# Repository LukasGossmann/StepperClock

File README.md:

# The clockwork
The clock hands are moved by 2 Nema8 double shaft stepper motors (one hollow shaft and one normal one).  
To allow the clock to move its hands smoothly and nearly completely silently the stepper motors are driven using 2 Trinamic TMC2209 SilentStepStick modules configured for 256x microstepping. `200 full steps * 256 micro steps = 51200 steps per rev`  
The structural parts of the clockwork are CNC cut from 3mm Resopal and slotted together.  
Unfortunately i mostly forgot to take pictures of the build process and the finished clockwork before installing it so only the CAD drawings show how everything fits together.

# The pendulum

Its driven by a small electromagnet at the frequency that the pendulum would naturally swing at.  
`Pendulum length = 350mm, Frequency = 0.8425Hz`  
The brass ring was made using a small ring rolling / metal bending machine and soldered together at the seam.  
For additional rigidity the pendulum shaft goes through the ring and is soldered to it at both the top and bottom.  
Inside of the ring are 2 circular slices of purple heart wood with slots for the shaft to pass through.  
They are just press fit in place and can be removed with a suction cup in case the brass needs to be re-polished.  

# The bell mechanism
Originally the design of the clock included a 5 tone bell mechanism that used solenoids which hit against brass rods.  
This part of the design was later abandoned due to the bells not sounding that good.  
The new design of the clockwork no longer includes the bells.  
There is a few pictures of the old assembly in the pictures folder.

<br clear="right"/>

# The dial plate

Its made from Corian that has been engraved with a 1mm carbide endmill.  
The engraving was then filled with black epoxy and a brass ring.  
After that everything was sanded flush and polished.  

<br clear="left"/>

# The electronics
The brain of this clock is a Raspberry Pi Pico. In total 4 PWM units are used to control the clock. 2 PWM units are used to drive the hands.  
The first PWM unit drives the minute hand at `(200 full steps * 256 microstepping)/(60 seconds * 60 minutes) = 14.22222222222222222Hz` which is still within reach of the PWM unit at normal system clock speeds.  
However the hour hand needs a step pulse at just 1/12th of this frequency `1.18518518519Hz` which is way too low for the PWM units to reach.  
So instead of generating the hour pulse directly, the second PWM unit is configured to be driven by the output of first pwn unit (using an external jumper) and just divides the frequency by 12.  
  
The same idea is also used to drive the very low frequency PWM output for the pendulum.  
In that case a 10khz clock is divided down to the desired frequency and the pulse width is adjustable as well for different power supply voltages.  

The time can be set through a text prompt via a USB serial terminal.  
When the time is set the clock hands automatically home, using 2 optical limit switches, and after that drive to the set time.  
At night the clock also goes into a power saving mode where the clock hands and the pendulum stop moving.  
When powering back up the clock hands home again and drive to the current time.  

There is unfortunately not very many pictures of the PCB itself because i again forgot to take pictures.  
I managed to find it in the background of some pictures of other projects though so i cropped out the unimportant bits (which is also why the quality of those pictures isn't great...)

<br clear="left"/>

# The lock

The lock is custom designed for this clock. It can be used for all types of full overlay doors when the door is at least 12mm or so thick (the lock is just 9mm thick).  
Once installed the lock and latch plate don't take up any space inside whatever enclosure they are used in.  
The latch of the lock is moved using an eccentric cam whose center of rotation is the key shaft.  
A small plastic spring is used to give some audible and haptic feedback on when the key has been rotated far enough.  

<br clear="right"/>

# The case
It was actually build as my journeyman's piece for the apprenticeship as a carpenter I completed in August of 2023.  
The case consists of 2 big half circles that were made by gluing ten 2mm pieces of veneer together while clamped to a mold.  
After the glue dries the pieces keep the shape and are actually surprisingly stiff.  
All the relevant documents that have to be submitted (Drawings, Concept, etc.) to get the project approved are also available in this repository for anyone interested.  
That is also why the repository contains a mix of German and English.  
To document the build process and show how certain things were made (in case anyone wants to replicate the project) I took a lot of pictures while building it.  
The clock was on display at the Forum Alstertal in Hamburg, Germany at the yearly exhibition of carpentry journeyman's pieces:  
`30th of June to the 05th July 2023`  
[Link to the event](https://www.forum-alstertal.de/news_veranstaltungen_detail_394.html)

# Awards

During the exhibition the residents living at the Forum Alstertal get the opportunity to vote on their favorite piece.
This year my clock won the audience award.

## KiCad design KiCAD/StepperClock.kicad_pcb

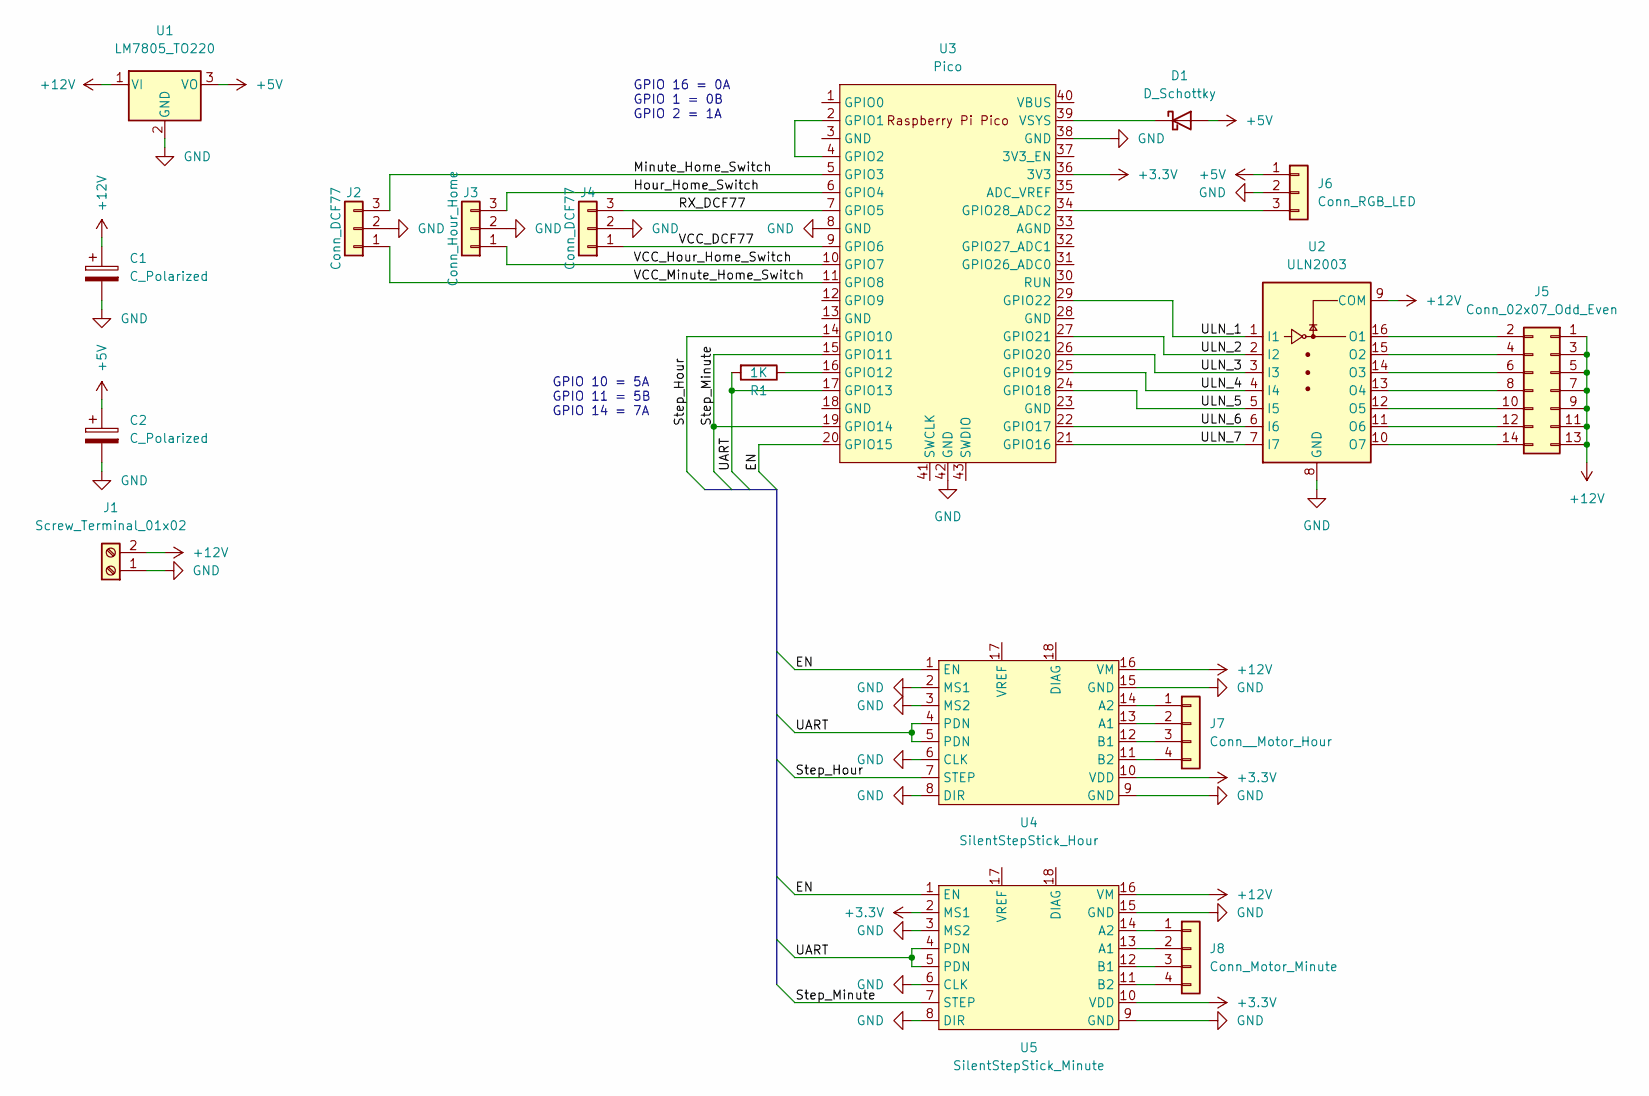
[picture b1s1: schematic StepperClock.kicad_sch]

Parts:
C1, C2: C_Polarized; CP_Radial_D10.0mm_P5.00mm_P7.50mm
D1: D_Schottky; D_DO-15_P10.16mm_Horizontal
J1: Screw_Terminal_01x02; TerminalBlock_RND_205-00232_1x02_P5.08mm_Horizontal
J2, J4: Conn_DCF77; PinHeader_1x03_P2.54mm_Vertical
J3: Conn_Hour_Home; PinHeader_1x03_P2.54mm_Vertical
J5: Conn_02x07_Odd_Even; PinHeader_2x07_P2.54mm_Vertical
J6: Conn_RGB_LED; PinHeader_1x03_P2.54mm_Vertical
J7: Conn__Motor_Hour; PinHeader_1x04_P2.54mm_Vertical
J8: Conn_Motor_Minute; PinHeader_1x04_P2.54mm_Vertical
R1: 1K; R_Axial_DIN0207_L6.3mm_D2.5mm_P10.16mm_Horizontal
U1: LM7805_TO220; TO-220-3_Vertical
U2: ULN2003; SOIC-16_3.9x9.9mm_P1.27mm
U3: Pico; RPi_Pico_SMD_TH
U4: SilentStepStick_Hour; SilentStepStick
U5: SilentStepStick_Minute; SilentStepStick

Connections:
+3.3V: U3.36 (3V3), U4.10 (VDD), U5.2 (MS1), U5.10 (VDD)
+5V: C2.1, D1.2 (A), J6.1, U1.3 (VO)
+12V: C1.1, J1.2, J5.1, J5.3, J5.5, J5.7, J5.9, J5.11, J5.13, U1.1 (VI), U2.9 (COM), U4.16 (VM), U5.16 (VM)
/EN: U3.20 (GPIO15), U4.1 (EN), U5.1 (EN)
/Hour_Home_Switch: J3.3, U3.6 (GPIO4)
/Minute_Home_Switch: J2.3, U3.5 (GPIO3)
/RX_DCF77: J4.3, U3.7 (GPIO5)
/Step_Hour: U3.14 (GPIO10), U4.7 (STEP)
/Step_Minute: U3.15 (GPIO11), U3.19 (GPIO14), U5.7 (STEP)
/UART: R1.2, U3.17 (GPIO13), U4.4 (PDN), U4.5 (PDN), U5.4 (PDN), U5.5 (PDN)
/ULN_1: U2.1 (I1), U3.29 (GPIO22)
/ULN_2: U2.2 (I2), U3.27 (GPIO21)
/ULN_3: U2.3 (I3), U3.26 (GPIO20)
/ULN_4: U2.4 (I4), U3.25 (GPIO19)
/ULN_5: U2.5 (I5), U3.24 (GPIO18)
/ULN_6: U2.6 (I6), U3.22 (GPIO17)
/ULN_7: U2.7 (I7), U3.21 (GPIO16)
/VCC_DCF77: J4.1, U3.9 (GPIO6)
/VCC_Hour_Home_Switch: J3.1, U3.10 (GPIO7)
/VCC_Minute_Home_Switch: J2.1, U3.11 (GPIO8)
GND: C1.2, C2.2, J1.1, J2.2, J3.2, J4.2, J6.2, U1.2 (GND), U2.8 (GND), U3.8 (GND), U3.38 (GND), U3.42 (GND), U4.2 (MS1), U4.3 (MS2), U4.6 (CLK), U4.8 (DIR), U4.9 (GND), U4.15 (GND), U5.3 (MS2), U5.6 (CLK), U5.8 (DIR), U5.9 (GND), U5.15 (GND)
unnamed: D1.1 (K), U3.39 (VSYS)
unnamed: J5.2, U2.16 (O1)
unnamed: J5.4, U2.15 (O2)
unnamed: J5.6, U2.14 (O3)
unnamed: J5.8, U2.13 (O4)
unnamed: J5.10, U2.12 (O5)
unnamed: J5.12, U2.11 (O6)
unnamed: J5.14, U2.10 (O7)
unnamed: J6.3, U3.34 (GPIO28_ADC2)
unnamed: J7.1, U4.14 (A2)
unnamed: J7.2, U4.13 (A1)
unnamed: J7.3, U4.12 (B1)
unnamed: J7.4, U4.11 (B2)
unnamed: J8.1, U5.14 (A2)
unnamed: J8.2, U5.13 (A1)
unnamed: J8.3, U5.12 (B1)
unnamed: J8.4, U5.11 (B2)
unnamed: U3.2 (GPIO1), U3.4 (GPIO2)
unnamed: R1.1, U3.16 (GPIO12)

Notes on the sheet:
GPIO 16 = 0A GPIO 1 = 0B GPIO 2 = 1A
GPIO 10 = 5A GPIO 11 = 5B GPIO 14 = 7A

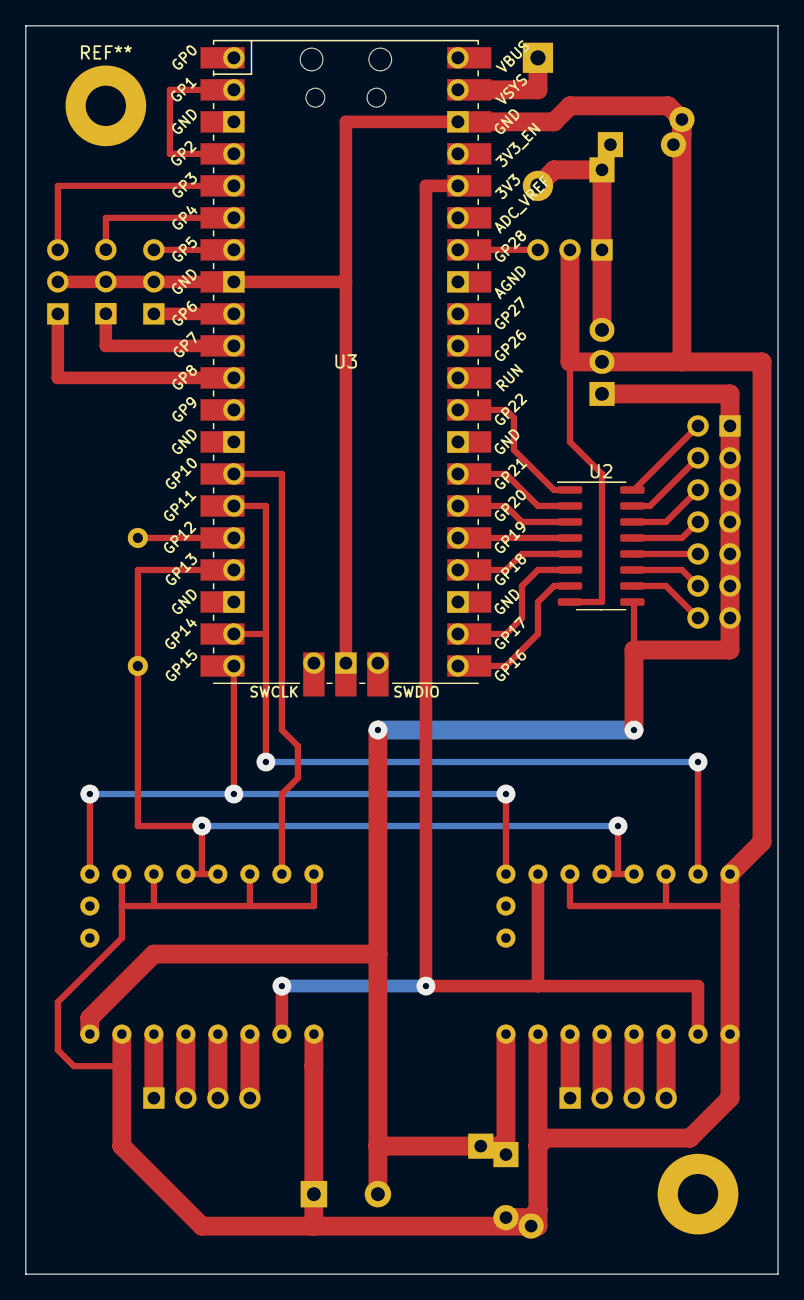
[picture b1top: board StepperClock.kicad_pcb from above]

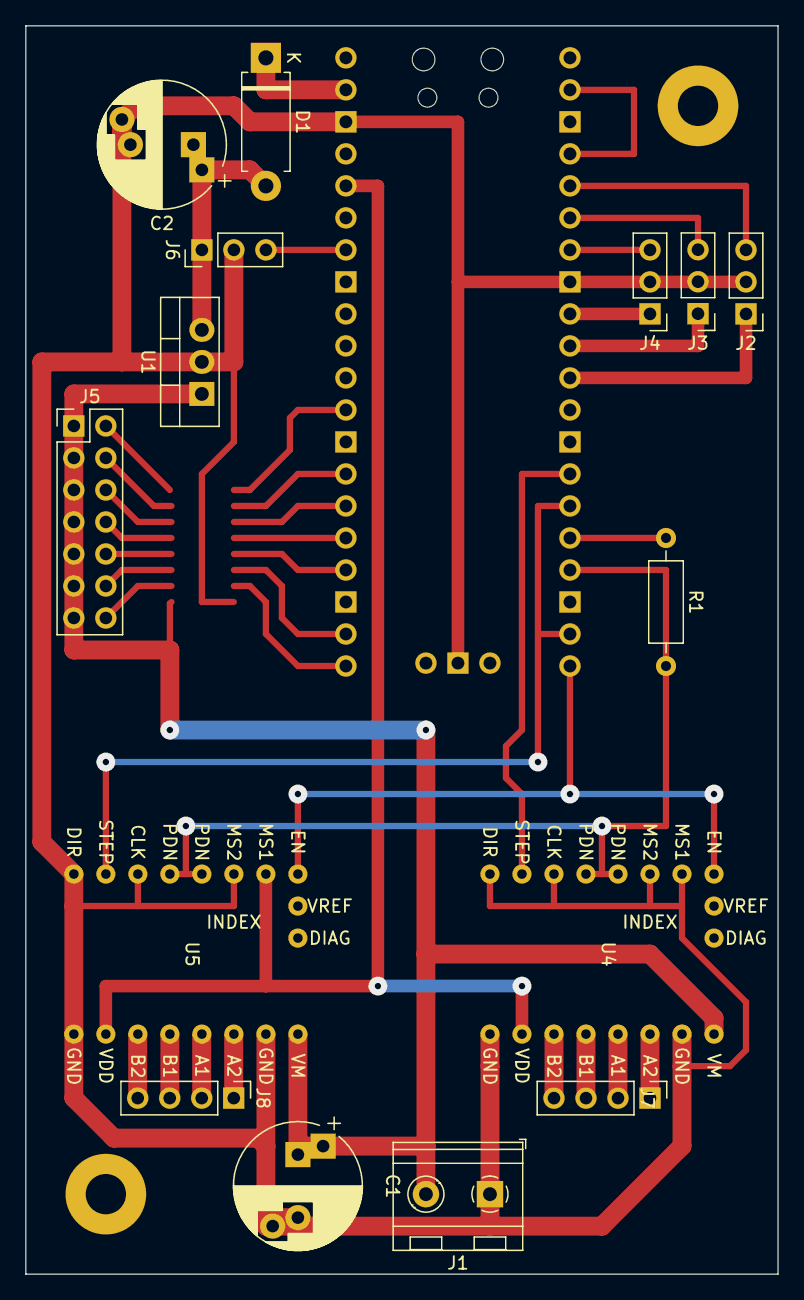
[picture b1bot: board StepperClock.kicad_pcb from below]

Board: 2 copper layers, 59.7 x 99.1 mm, 17 parts (15 on the bottom side), 40 nets.

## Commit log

2023-06-22 Initial commit (removing history)
2023-06-25 Added picures and updated ReadMe
2023-07-26 Made 3D models look nicer and updated readme with pictures
2023-11-11 Long overdue updates
